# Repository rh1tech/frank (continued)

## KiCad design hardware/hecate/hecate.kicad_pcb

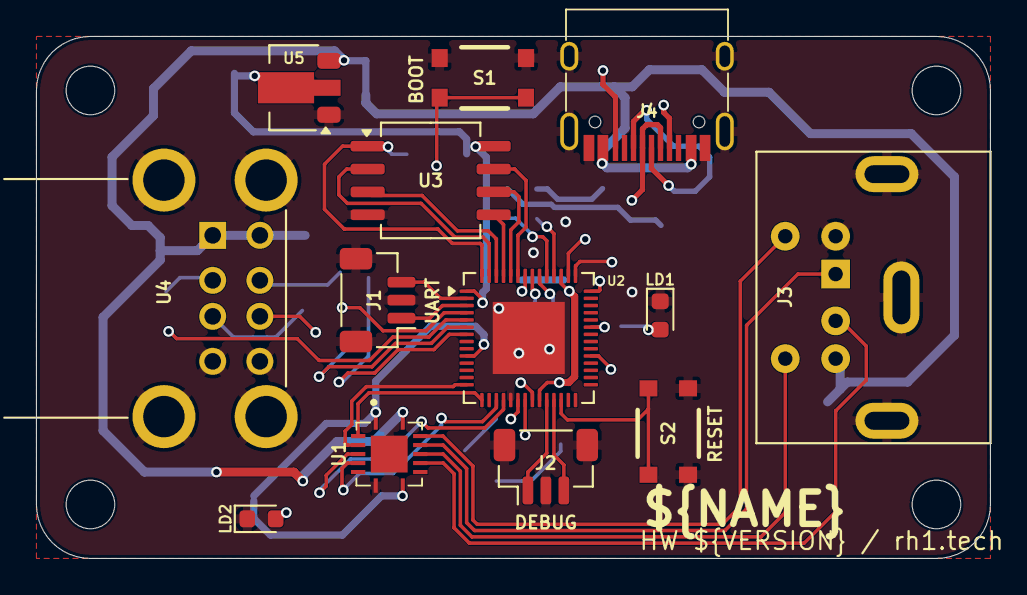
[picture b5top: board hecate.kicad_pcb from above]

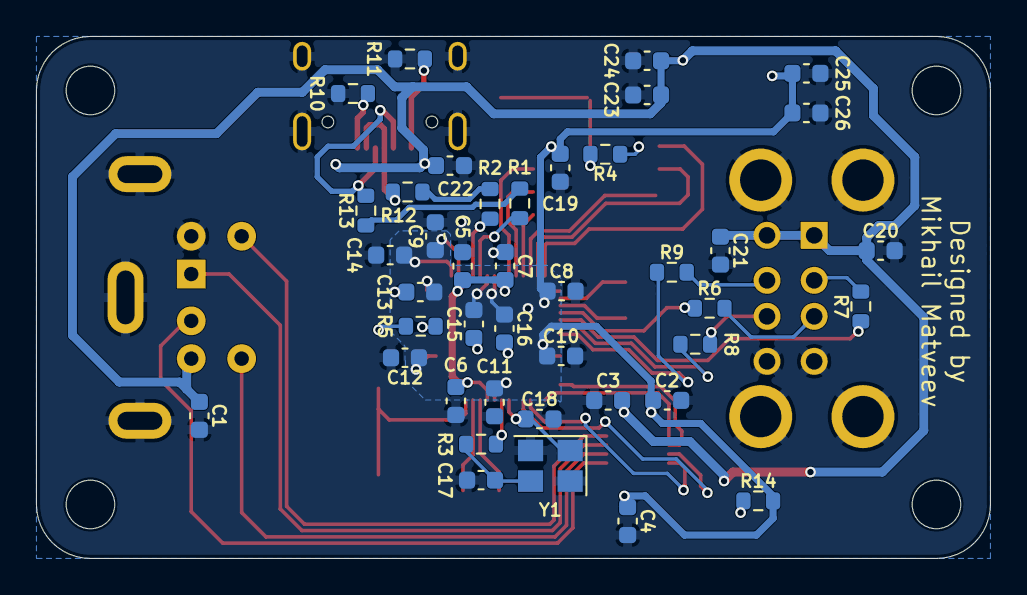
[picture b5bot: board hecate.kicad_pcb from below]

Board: 2 copper layers, 53.0 x 29.0 mm, 58 parts (41 on the bottom side), 46 nets.

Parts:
C1, C2, C3, C4, C5, C6, C8, C10, C11, C12, C13, C14, C15, C16, C19, C22, C24, C26: 100n; C_0603_1608Metric
C7, C9: 1u; C_0603_1608Metric
C17, C18: 15p; C_0603_1608Metric
C20, C21, C23, C25: 10u; C_0603_1608Metric
H1, H2, H3, H4: MountingHole; MountingHole_2.7mm
J1: UART; JST_SH_BM03B-SRSS-TB_1x03-1MP_P1.00mm_Vertical
J2: DEBUG; JST_SH_BM03B-SRSS-TB_1x03-1MP_P1.00mm_Vertical
J3: MDC-036; MiniDIN_6pin_Female
J4: USB4215-03-A; USB_C_Receptacle
LD1: Blue; LED_0603_1608Metric
LD2: Green; LED_0603_1608Metric
R1, R2: 27R; R_0603_1608Metric
R3, R4, R5, R14: 1K; R_0603_1608Metric
R6, R7, R8, R9, R12, R13: 22R; R_0603_1608Metric
R10, R11: 5.1K; R_0603_1608Metric
S1, S2: RP Reset; KMR_2
U1: TXS0104ERGYR; RGY_S-PVQFN-N14_
U2: RP2040; QFN-56-1EP_7x7mm_P0.4mm_EP4x4mm
U3: W25Q128JVSIQ; SOIC-8
U4: USB_A_Stacked
U5: AMS1117-3.3; SOT-89-3
Y1: 12 MHz; Crystal_SMD_3225-4Pin

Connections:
+3V3: C2.1, C4.1, C8.1, C9.1, C10.1, C11.1, C12.1, C13.1, C14.1, C15.1, C16.1, C19.1, C25.2, C26.2, R14.2, U1.1 (VCCA), U1.8 (OE), U2.1 (IOVDD), U2.10 (IOVDD), U2.22 (IOVDD), U2.33 (IOVDD), U2.42 (IOVDD), U2.43 (ADC_AVDD), U2.44 (VREG_IN), U2.48 (USB_VDD), U2.49 (IOVDD), U3.8 (VCC), U5.2 (VO)
/GPIO2: R6.1, U2.4 (GPIO2)
/GPIO3: R7.1, U2.5 (GPIO3)
/GPIO4: R8.1, U2.6 (GPIO4)
/GPIO5: R9.1, U2.7 (GPIO5)
/GPIO11: U1.3 (A2), U2.14 (GPIO11)
/GPIO12: U1.2 (A1), U2.15 (GPIO12)
/GPIO14: U1.5 (A4), U2.17 (GPIO14)
/GPIO15: U1.4 (A3), U2.18 (GPIO15)
/PS2/KB_CLK_5V: J3.5, U1.13 (B1)
/PS2/KB_DATA_5V: J3.1, U1.12 (B2)
/PS2/MS_CLK_5V: J3.6, U1.11 (B3)
/PS2/MS_DATA_5V: J3.2, U1.10 (B4)
/RP2040/BOOT: R4.2, S1.2, S1.4
/RP2040/D+: R1.1, R13.1
/RP2040/D-: R2.1, R12.1
/RP2040/GPIO0: J1.1, U2.2 (GPIO0)
/RP2040/GPIO1: J1.3, U2.3 (GPIO1)
/RP2040/GPIO25: R5.2, U2.37 (GPIO25)
/RP2040/QSPI_SCLK: U2.52 (QSPI_SCLK), U3.6 (CLK)
/RP2040/QSPI_SD0: U2.53 (QSPI_SD0), U3.5 (DI(IO0))
/RP2040/QSPI_SD1: U2.55 (QSPI_SD1), U3.2 (DO(IO1))
/RP2040/QSPI_SD2: U2.54 (QSPI_SD2), U3.3 (IO2)
/RP2040/QSPI_SD3: U2.51 (QSPI_SD3), U3.7 (IO3)
/RP2040/QSPI_SS: R4.1, U2.56 (QSPI_SS), U3.1 (~CS)
/RP2040/RUN: S2.2, S2.4, U2.26 (RUN)
/RP2040/SWCLK: J2.3, U2.24 (SWCLK)
/RP2040/SWD: J2.1, U2.25 (SWD)
/RP2040/XIN: C18.1, U2.20 (XIN), Y1.1
/RP2040/XOUT: R3.1, U2.21 (XOUT)
GND: C1.2, C2.2, C3.2, C4.2, C5.2, C6.2, C7.2, C8.2, C9.2, C10.2, C11.2, C12.2, C13.2, C14.2, C15.2, C16.2, C17.2, C18.2, C19.2, C20.2, C21.2, C22.1, C23.1, C24.1, C25.1, C26.1, J1.2, J2.2, J3.3, J4.1 (GND), J4.12 (GND), J4.13 (SHIELD), LD1.1 (K), LD2.1 (K), R10.1, R11.1, S1.1, S1.3, S2.1, S2.3, U1.7 (GND), U1.15 (THERMAL_PAD), U2.19 (TESTEN), U2.57 (GND), U3.4 (GND), U4.4 (GND1), U4.8 (GND2), U4.SH (Shield), U5.1 (GND), Y1.2 (G), Y1.4 (G)
unnamed: C17.1, R3.2, Y1.3
unnamed: J4.4 (CC1), R10.2
unnamed: J4.10 (CC2), R11.2
unnamed: J4.5 (DN2), J4.7 (DN1), R12.2
unnamed: J4.6 (DP1), J4.8 (DP2), R13.2
unnamed: LD1.2 (A), R5.1
unnamed: LD2.2 (A), R14.1
unnamed: R2.2, U2.46 (USB_DM)
unnamed: R1.2, U2.47 (USB_DP)
unnamed: C5.1, C6.1, C7.1, U2.23 (DVDD), U2.45 (VREG_VOUT), U2.50 (DVDD)
unnamed: R6.2, U4.3 (D1+)
unnamed: R7.2, U4.2 (D1-)
unnamed: R8.2, U4.7 (D2+)
unnamed: R9.2, U4.6 (D2-)
VBUS: C1.1, C3.1, C20.1, C21.1, C22.2, C23.2, C24.2, J3.4, J4.2 (VBUS), J4.11 (VBUS), U1.14 (VCCB), U4.1 (VBUS1), U4.5 (VBUS2), U5.3 (VI)

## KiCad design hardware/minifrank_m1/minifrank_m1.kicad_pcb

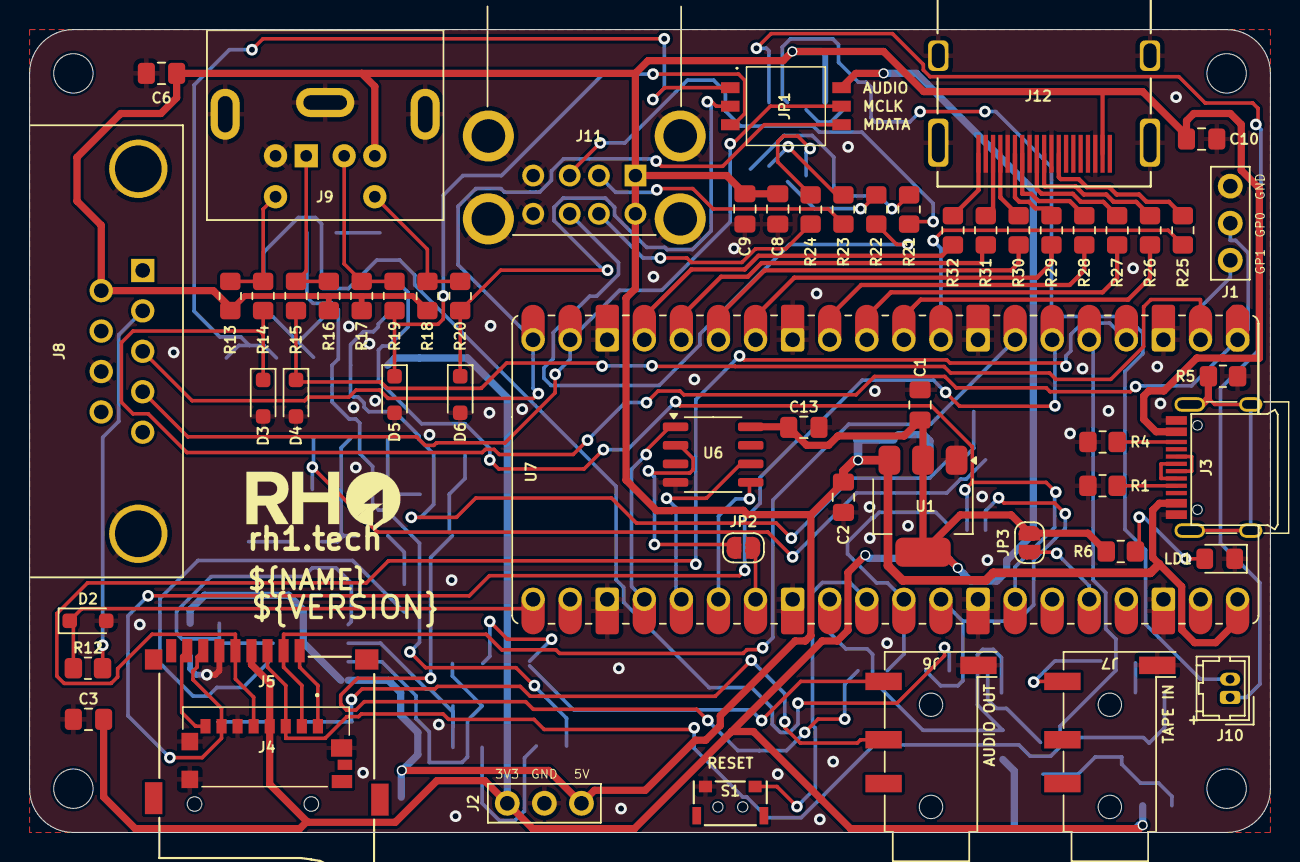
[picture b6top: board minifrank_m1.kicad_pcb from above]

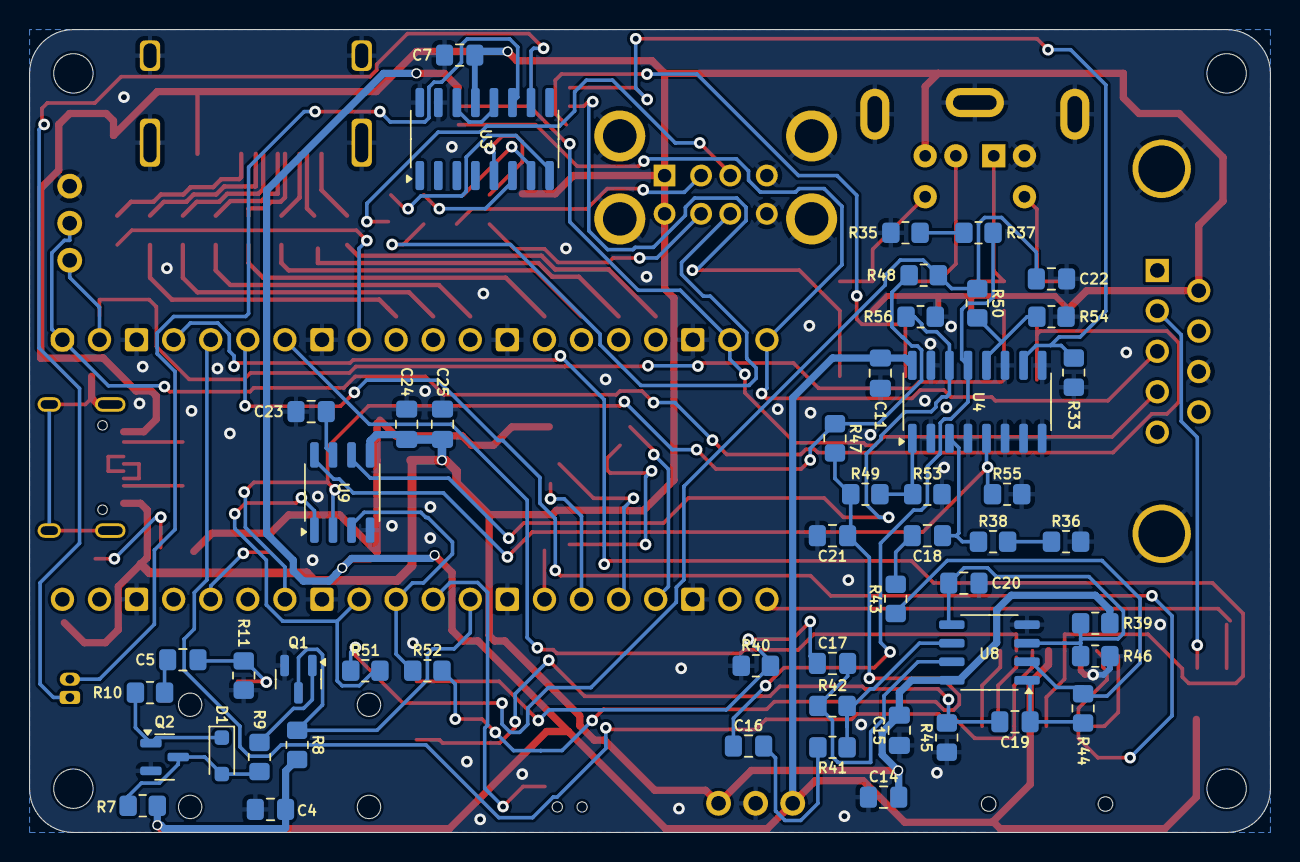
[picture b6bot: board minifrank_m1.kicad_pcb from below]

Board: 2 copper layers, 85.0 x 55.0 mm, 113 parts (51 on the bottom side), 91 nets.

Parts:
C1, C2, C8, C9, C14, C16, C17, C18, C19, C20, C23, C24: 10u; Capacitor (0805)
C3, C4, C5, C6, C10, C11, C13, C15, C25: 100n; Capacitor (0805)
C7: 4.7u; Capacitor (0805)
C21, C22: 47n; Capacitor (0805)
D1: 1N4148; Diode (SOD-323)
D2, D3, D4, D5, D6: 3V3; Diode (SOD-323)
H1, H2, H3, H4: MountingHole; Mounting Hole (2.7mm)
J1: UART; Pin Header (1x03)
J2: PWR; Pin Header (1x03)
J3: USB4215-03-A; USB Type C
J4: 0475710001; MicroSD (SMD, short)
J5: 104031-0811; MicroSD (SMD, long)
J6, J7: PJ-320D; Jack (3.5mm, PJ-320D)
J8: D-SUB 9 Male; D-SUB (9 pin, male, top mount)
J9: MDC-036; MiniDIN (6 Pin, female)
J10: USB HUB Data; Connector Female 1.25 JST 2P
J11: SS-52100-004; USB Type A (stacked)
J12: DC3RX19JA2; HDMI (female)
JP1: Main Jumpers; DS05127203BKSMTTR
JP2, JP3: Jumper (Solder); Jumper (solder)
LD1: Power; LED (0805)
Q1, Q2: BC850; SOT-23
R1, R4: 5.1K; Resistor (0805)
R5: 1M; Resistor (0805)
R6, R8, R12, R13, R16, R17, R18, R51, R52: 1K; Resistor (0805)
R7, R9, R10, R33, R37, R38, R39, R41, R43, R46, R49, R50: 10K; Resistor (0805)
R11, R14, R15, R19, R20: 100R; Resistor (0805)
R21, R22, R23, R24: 22R; Resistor (0805)
R25, R26, R27, R28, R29, R30, R31, R32: 270R; Resistor (0805)
R35, R36, R47, R48, R53, R54: 2K; Resistor (0805)
R40, R45: 20K; Resistor (0805)
R42, R44: 47K; Resistor (0805)
R55, R56: 470R; Resistor (0805)
S1: Reset; TACT-SIDE-4623
U1: NCP1117 3.3; SOT-223
U3: MW7211A; SOP-16
U4: 74HC4052D; SOP-16
U6: ESP-PSRAM32; SO-8
U7: Rasberry Pi Pico; Raspberry Pi Pico
U8: LM358; SO-8
U9: TDA1387T; SO-8

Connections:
+3V3: C1.1, C3.2, C4.1, C11.2, C13.1, J2.1, J4.P4 (VDD), J5.4 (VDD), JP1.6, JP3.2 (B), R6.2, R7.1, R8.1, U1.2 (VO), U4.16 (VCC), U6.8 (VCC)
/AMP_IN_L: C16.1, R37.1, U4.13 (1Z)
/AMP_IN_R: C18.1, R38.1, U4.3 (2Z)
/AUDIOSW: JP1.1, R33.2, U4.10 (S0)
/Audio Out/AMP_OUTL: C17.2, J6.T, R40.2
/Audio Out/AMP_OUTR: C19.2, J6.R, R45.2
/GPIO0: D3.1 (K), J1.2, R14.2, U7.1 (GPIO0)
/GPIO1: D4.1 (K), J1.3, R15.2, U7.2 (GPIO1)
/GPIO2: J4.P5 (CLK), J5.5 (CLK), U7.4 (GPIO2)
/GPIO3: J4.P3 (CMD), J5.3 (CMD), U7.5 (GPIO3)
/GPIO4: J4.P7 (DAT0), J5.7 (DAT0), U7.6 (GPIO4)
/GPIO5: J4.P2 (CD/DAT3), J5.2 (DAT3/CD), U7.7 (GPIO5)
/GPIO6: R25.2, U7.9 (GPIO6)
/GPIO7: R26.2, U7.10 (GPIO7)
/GPIO8: R27.2, U7.11 (GPIO8)
/GPIO9: R28.2, U7.12 (GPIO9)
/GPIO10: R29.2, U7.14 (GPIO10)
/GPIO11: R30.2, U7.15 (GPIO11)
/GPIO12: R31.2, U7.16 (GPIO12)
/GPIO13: R32.2, U7.17 (GPIO13)
/GPIO14: J8.4, JP1.5, U7.19 (GPIO14)
/GPIO15: J8.3, JP1.4, U7.20 (GPIO15)
/GPIO16: D2.1 (K), R12.1, U7.21 (GPIO16)
/GPIO18: U6.1 (~CE), U7.24 (GPIO18)
/GPIO19: U6.6 (SCLK), U7.25 (GPIO19)
/GPIO20: U6.5 (SI/SIO), U7.26 (GPIO20)
/GPIO21: JP2.2 (B), U7.27 (GPIO21)
/GPIO22: Q1.3 (C), R8.2, U7.29 (GPIO22)
/GPIO26: R52.2, U7.31 (GPIO26_ADC0), U9.3 (DATA)
/GPIO27: R51.2, U7.32 (GPIO27_ADC1), U9.1 (SCLK)
/GPIO28: R47.1, R48.1, U7.34 (GPIO28_ADC2), U9.2 (LRCK)
/KB_CLK: J9.5, R13.2, R14.1
/KB_DATA: J9.1, R15.1, R16.2
/MS_CLK: J9.6, R18.2, R20.1
/MS_CLK_3V: D6.1 (K), JP1.2, R20.2
/MS_DATA: J9.2, R17.2, R19.1
/MS_DATA_3V: D5.1 (K), JP1.3, R19.2
/PWM_OUT_L: R50.2, R54.1, U4.12 (1Y0)
/PWM_OUT_R: R49.2, R53.1, U4.1 (2Y0)
/Power/D+: J3.6 (DP1), J3.8 (DP2)
/Power/D-: J3.5 (DN2), J3.7 (DN1)
/RUN: S1.1, U7.30 (RUN)
/SD Card/DAT1: J4.P8 (DAT1), J5.8 (DAT1)
/SD Card/DAT2: J4.P1 (DAT2), J5.1 (DAT2)
/TDA_L: R56.2, U4.14 (1Y1), U9.6 (A_LEFT)
/TDA_R: R55.1, U4.5 (2Y1), U9.8 (A_RIGHT)
/USB Hub/DM_IN: J10.2, U3.10 (DMU)
/USB Hub/DP_IN: J10.1, U3.11 (DPU)
/USB_D1+: R21.1, U3.8 (DP3)
/USB_D1-: R23.1, U3.7 (DM3)
/USB_D2+: R22.1, U3.6 (DP2)
/USB_D2-: R24.1, U3.5 (DM2)
GND: C1.2, C2.2, C3.1, C4.2, C6.2, C7.2, C8.2, C9.2, C10.2, C11.1, C13.2, C14.1, C15.1, C20.1, C21.2, C22.2, C23.2, C24.2, C25.2, D2.2 (A), D3.2 (A), D4.2 (A), D5.2 (A), D6.2 (A), J1.1, J2.2, J3.1 (GND), J3.12 (GND), J4.G1 (GND_1), J4.G2 (GND_2), J4.G3 (GND_3), J4.P6 (VSS), J5.6 (VSS), J6.S, J7.S, J8.8, J9.3, J11.4 (GND1), J11.8 (GND2), J11.9 (Shield), J12.2 (G_D2), J12.5 (G_D1), J12.8 (G_D0), J12.11 (G_CLK), J12.17 (G_DDC/CEC), J12.20 (SHIELD1), J12.21 (SHIELD2), J12.22 (SHIELD3), J12.23 (SHIELD4), LD1.1 (K), Q1.2 (E), Q2.2 (E), R1.1, R4.1, R5.2, R11.2, R33.1, R35.2, R36.2, R40.1, R45.1, R46.1, R53.2, R54.2, R55.2, R56.1, S1.2, U1.1 (GND), U3.15 (GND), U3.16 (GND), U4.2 (2Y2), U4.4 (2Y3), U4.6 (~E), U4.7 (VEE), U4.8 (GND), U4.9 (S1), U4.11 (1Y3), U4.15 (1Y2), U6.4 (VSS), U7.3 (GND), U7.8 (GND), U7.13 (GND), U7.18 (GND), U7.23 (GND), U7.28 (GND), U7.33 (AGND), U7.38 (GND), U8.4 (V-), U9.4 (AGND)
unnamed: C5.1, J7.T, R11.1
unnamed: C5.2, R10.1
unnamed: C16.2, R41.2
unnamed: C17.1, R42.1, U8.7
unnamed: C18.2, R43.2
unnamed: C19.1, R44.1, U8.1
unnamed: C21.1, R47.2, R49.1, R52.1
unnamed: C22.1, R48.2, R50.1, R51.1
unnamed: D1.2 (A), Q2.3 (C), R7.2, R9.1
unnamed: D1.1 (K), Q2.1 (B), R10.2
unnamed: J3.4 (CC1), R1.2
unnamed: J3.10 (CC2), R4.2
unnamed: J3.13 (SHIELD), R5.1
unnamed: J8.2, R12.2
unnamed: J11.3 (D1+), R21.2
unnamed: J11.2 (D1-), R23.2
unnamed: J11.7 (D2+), R22.2
unnamed: J11.6 (D2-), R24.2
unnamed: J12.12 (CLKN), R25.1
unnamed: J12.10 (CLKP), R26.1
unnamed: J12.9 (D0N), R27.1
unnamed: J12.7 (D0P), R28.1
unnamed: J12.6 (D1N), R29.1
unnamed: J12.4 (D1P), R30.1
unnamed: J12.3 (D2N), R31.1
unnamed: J12.1 (D2P), R32.1
unnamed: JP2.1 (A), U6.2 (SO/SIO)
unnamed: JP3.1 (A), U7.36 (3V3)
unnamed: LD1.2 (A), R6.1
unnamed: Q1.1 (B), R9.2
unnamed: R35.1, R37.2
unnamed: R36.1, R38.2
unnamed: U3.12 (VD33), U3.14 (VD3)
unnamed: C20.2, R39.1, R46.2, U8.3 (+), U8.5 (+)
unnamed: R43.1, R44.2, U8.2 (-)
unnamed: R41.1, R42.2, U8.6 (-)
unnamed: C23.1, U9.7 (FLT)
VBUS: C2.1, C6.1, C7.1, C8.1, C9.1, C10.1, C14.2, C15.2, C24.1, C25.1, J2.3, J3.2 (VBUS), J3.11 (VBUS), J8.6, J9.4, J11.1 (VBUS1), J11.5 (VBUS2), J12.18 (+5V), R13.1, R16.1, R17.1, R18.1, R39.2, U1.3 (VI), U3.13 (VDD5), U7.40 (VBUS), U8.8 (V+), U9.5 (VA)

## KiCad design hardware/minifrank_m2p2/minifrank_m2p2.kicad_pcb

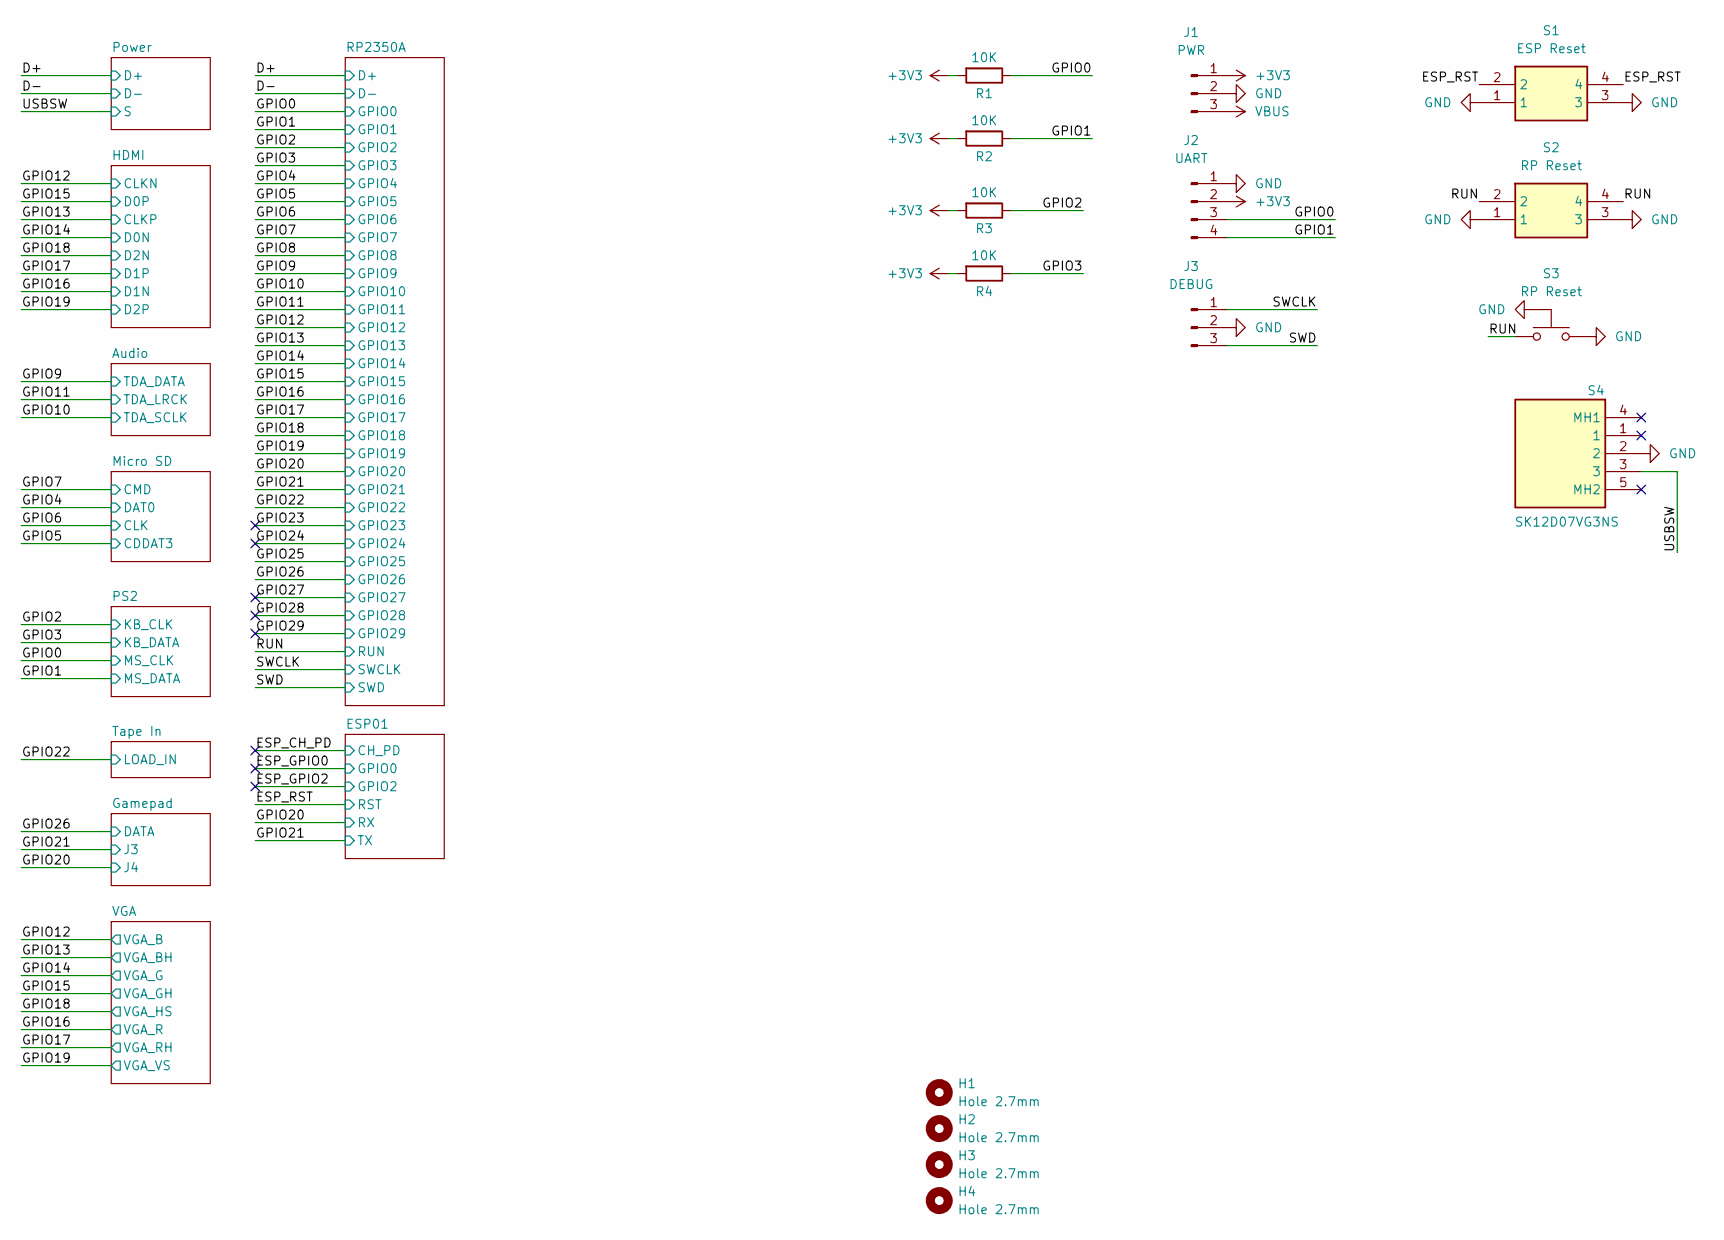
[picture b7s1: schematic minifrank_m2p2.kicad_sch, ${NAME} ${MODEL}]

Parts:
H1, H2, H3, H4: Hole 2.7mm; Mounting Hole (2.7mm)
J1: PWR; Pin Header (1x03)
J2: UART; JST_SH_BM04B-SRSS-TB_1x04-1MP_P1.00mm_Vertical
J3: DEBUG; JST_SH_BM03B-SRSS-TB_1x03-1MP_P1.00mm_Vertical
R1, R2, R3, R4: 10K; R_0603_1608Metric
S1: ESP Reset; KMR_2; Mouser Part Number 611-KMR221G-LFS
S2: RP Reset; KMR_2; Mouser Part Number 611-KMR221G-LFS
S3: RP Reset; TS-1234VW
S4: SK12D07VG3NS; Mouser Part Number 611-SK12D07VG3NS

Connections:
+3V3: J1.1, J2.2, R1.2, R2.2, R3.2, R4.2; also elsewhere on the board
/ESP_RST: S1.2, S1.4; also elsewhere on the board
/GPIO0: J2.3, R1.1; also elsewhere on the board
/GPIO1: J2.4, R2.1; also elsewhere on the board
/GPIO2: R3.1; also elsewhere on the board
/GPIO3: R4.1; also elsewhere on the board
/RUN: S2.2, S2.4, S3.1; also elsewhere on the board
/SWCLK: J3.1; also elsewhere on the board
/SWD: J3.3; also elsewhere on the board
/USBSW: S4.3; also elsewhere on the board
GND: J1.2, J2.1, J3.2, S1.1, S1.3, S2.1, S2.3, S3.2, S3.3 (GND), S4.2; also elsewhere on the board
VBUS: J1.3; also elsewhere on the board

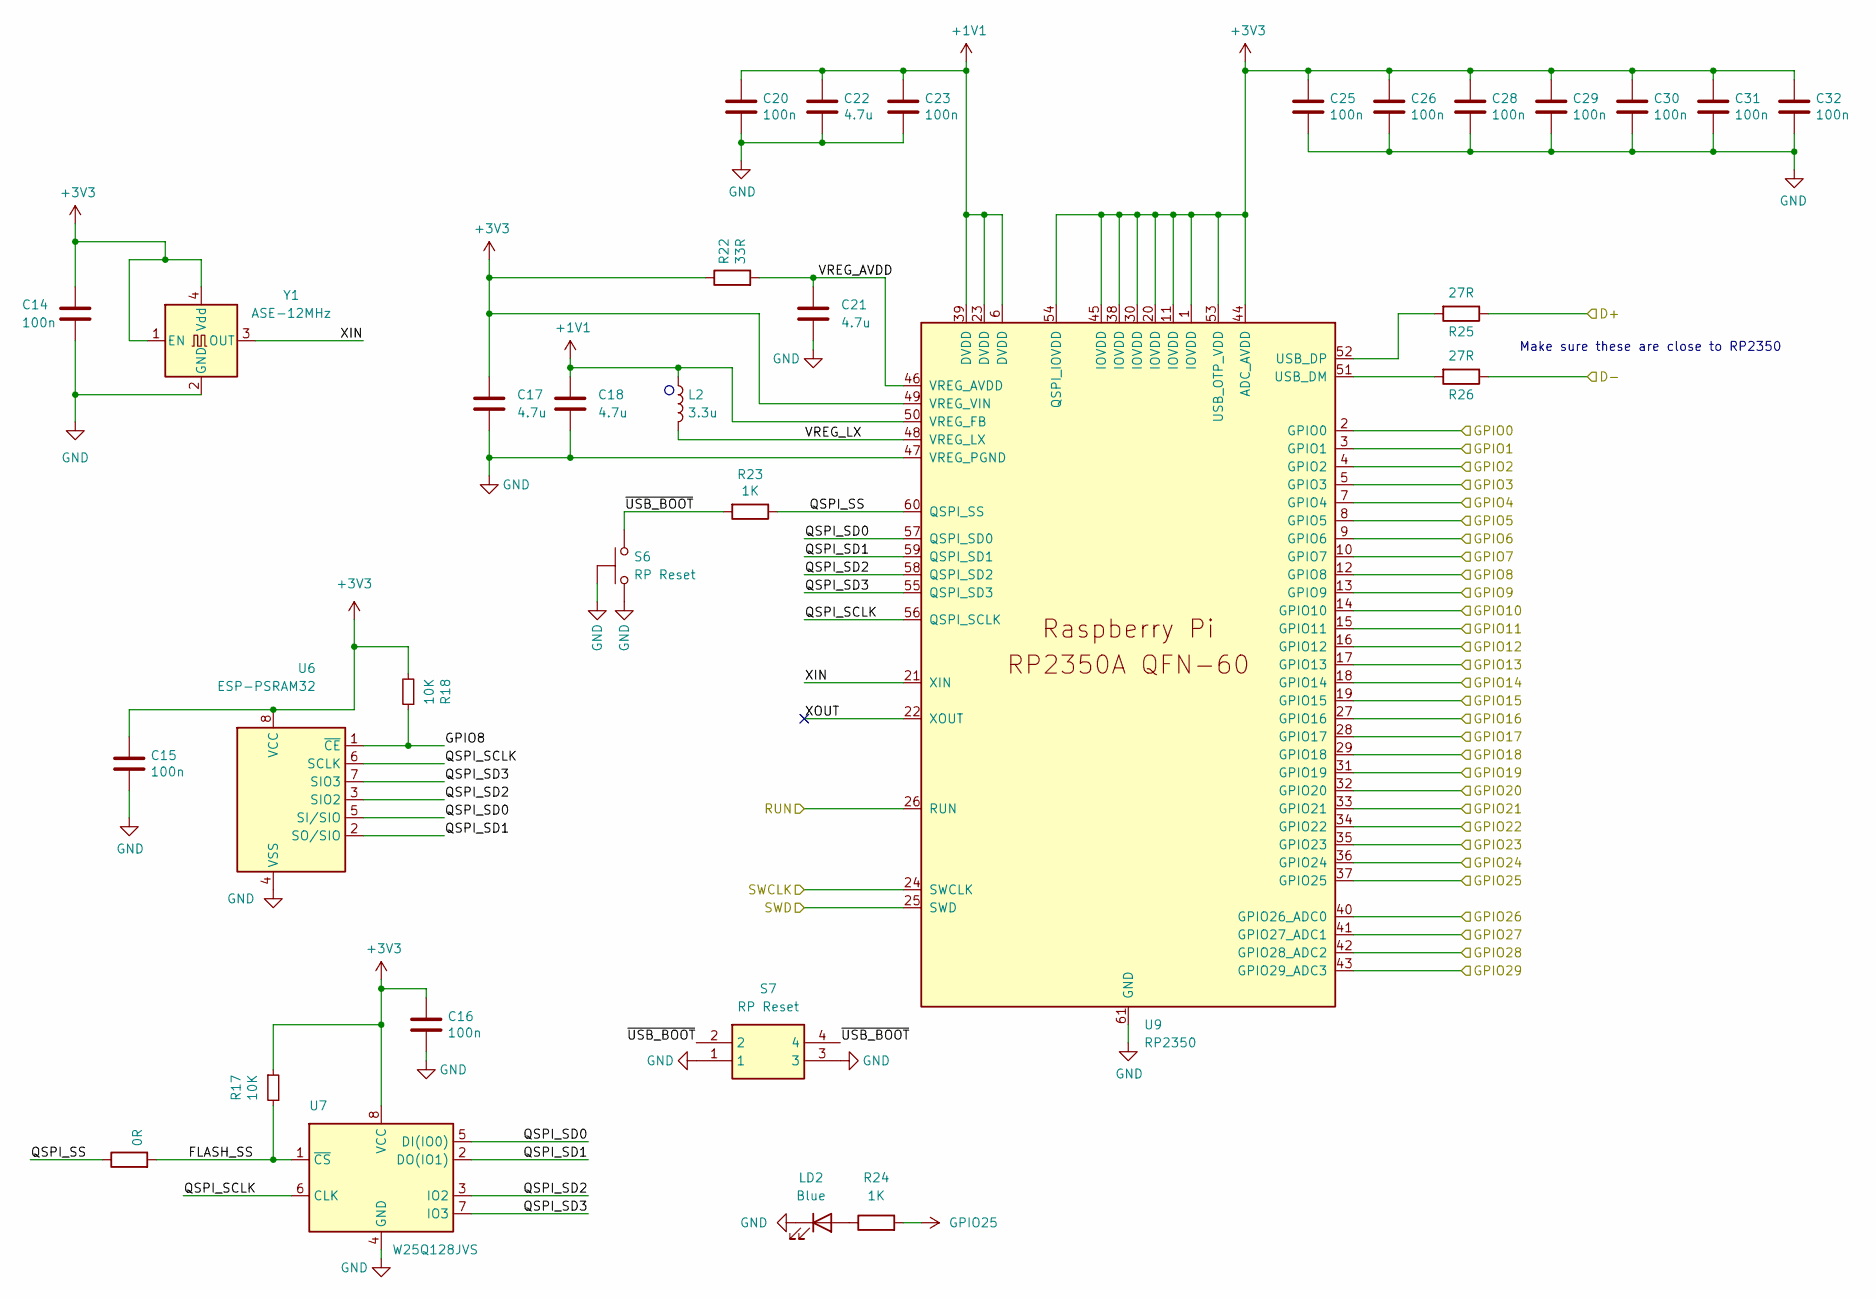
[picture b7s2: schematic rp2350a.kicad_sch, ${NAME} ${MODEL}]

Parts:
C14, C15, C16, C20, C23, C25, C26, C28, C29, C30, C31, C32: 100n; C_0603_1608Metric
C17, C18, C21, C22: 4.7u; C_0603_1608Metric
L2: 3.3u; L_pol_2016
LD2: Blue; LED_0603_1608Metric
R16: 0R; R_0603_1608Metric
R17, R18: 10K; R_0603_1608Metric
R22: 33R; R_0603_1608Metric
R23, R24: 1K; R_0603_1608Metric
R25, R26: 27R; R_0603_1608Metric
S6: RP Reset; TS-1234VW
S7: RP Reset; KMR_2; Mouser Part Number 611-KMR221G-LFS
U6: ESP-PSRAM32; SO-8
U7: W25Q128JVS; SOIC-8
U9: RP2350; QFN 60 (RP2350A)
Y1: ASE-12MHz; Oscillator_SMD_Abracon_ASE-4Pin_3.2x2.5mm

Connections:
+1V1: C18.1, C20.1, C22.1, C23.1, L2.1, U9.6 (DVDD), U9.23 (DVDD), U9.39 (DVDD), U9.50 (VREG_FB)
+3V3: C14.1, C15.1, C16.1, C17.1, C25.1, C26.1, C28.1, C29.1, C30.1, C31.1, C32.1, R17.1, R18.2, R22.1, U6.8 (VCC), U7.8 (VCC), U9.1 (IOVDD), U9.11 (IOVDD), U9.20 (IOVDD), U9.30 (IOVDD), U9.38 (IOVDD), U9.44 (ADC_AVDD), U9.45 (IOVDD), U9.49 (VREG_VIN), U9.53 (USB_OTP_VDD), U9.54 (QSPI_IOVDD), Y1.1 (EN), Y1.4 (Vdd); also elsewhere on the board
/D+: R25.1; also elsewhere on the board
/D-: R26.1; also elsewhere on the board
/GPIO0: U9.2 (GPIO0); also elsewhere on the board
/GPIO1: U9.3 (GPIO1); also elsewhere on the board
/GPIO2: U9.4 (GPIO2); also elsewhere on the board
/GPIO3: U9.5 (GPIO3); also elsewhere on the board
/GPIO4: U9.7 (GPIO4); also elsewhere on the board
/GPIO5: U9.8 (GPIO5); also elsewhere on the board
/GPIO6: U9.9 (GPIO6); also elsewhere on the board
/GPIO7: U9.10 (GPIO7); also elsewhere on the board
/GPIO8: R18.1, U6.1 (~CE), U9.12 (GPIO8)
/GPIO9: U9.13 (GPIO9); also elsewhere on the board
/GPIO10: U9.14 (GPIO10); also elsewhere on the board
/GPIO11: U9.15 (GPIO11); also elsewhere on the board
/GPIO12: U9.16 (GPIO12); also elsewhere on the board
/GPIO13: U9.17 (GPIO13); also elsewhere on the board
/GPIO14: U9.18 (GPIO14); also elsewhere on the board
/GPIO15: U9.19 (GPIO15); also elsewhere on the board
/GPIO16: U9.27 (GPIO16); also elsewhere on the board
/GPIO17: U9.28 (GPIO17); also elsewhere on the board
/GPIO18: U9.29 (GPIO18); also elsewhere on the board
/GPIO19: U9.31 (GPIO19); also elsewhere on the board
/GPIO20: U9.32 (GPIO20); also elsewhere on the board
/GPIO21: U9.33 (GPIO21); also elsewhere on the board
/GPIO22: U9.34 (GPIO22); also elsewhere on the board
/GPIO23: U9.35 (GPIO23)
/GPIO24: U9.36 (GPIO24)
/GPIO26: U9.40 (GPIO26_ADC0); also elsewhere on the board
/GPIO27: U9.41 (GPIO27_ADC1)
/GPIO28: U9.42 (GPIO28_ADC2)
/GPIO29: U9.43 (GPIO29_ADC3)
/RP2350A/FLASH_SS: R16.2, R17.2, U7.1 (~CS)
/RP2350A/QSPI_SCLK: U6.6 (SCLK), U7.6 (CLK), U9.56 (QSPI_SCLK)
/RP2350A/QSPI_SD0: U6.5 (SI/SIO), U7.5 (DI(IO0)), U9.57 (QSPI_SD0)
/RP2350A/QSPI_SD1: U6.2 (SO/SIO), U7.2 (DO(IO1)), U9.59 (QSPI_SD1)
/RP2350A/QSPI_SD2: U6.3 (SIO2), U7.3 (IO2), U9.58 (QSPI_SD2)
/RP2350A/QSPI_SD3: U6.7 (SIO3), U7.7 (IO3), U9.55 (QSPI_SD3)
/RP2350A/QSPI_SS: R16.1, R23.1, U9.60 (QSPI_SS)
/RP2350A/VREG_AVDD: C21.1, R22.2, U9.46 (VREG_AVDD)
/RP2350A/VREG_LX: L2.2, U9.48 (VREG_LX)
/RP2350A/XIN: U9.21 (XIN), Y1.3 (OUT)
/RP2350A/XOUT: U9.22 (XOUT)
/RP2350A/~USB_BOOT: R23.2, S6.2, S7.2, S7.4
/RUN: U9.26 (RUN); also elsewhere on the board
/SWCLK: U9.24 (SWCLK); also elsewhere on the board
/SWD: U9.25 (SWD); also elsewhere on the board
GND: C14.2, C15.2, C16.2, C17.2, C18.2, C20.2, C21.2, C22.2, C23.2, C25.2, C26.2, C28.2, C29.2, C30.2, C31.2, C32.2, LD2.1 (K), S6.1, S6.3 (GND), S7.1, S7.3, U6.4 (VSS), U7.4 (GND), U9.47 (VREG_PGND), U9.61 (GND), Y1.2 (GND); also elsewhere on the board
GPIO25: R24.2, U9.37 (GPIO25)
unnamed: LD2.2 (A), R24.1
unnamed: R26.2, U9.51 (USB_DM)
unnamed: R25.2, U9.52 (USB_DP)

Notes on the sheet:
Make sure these are close to RP2350

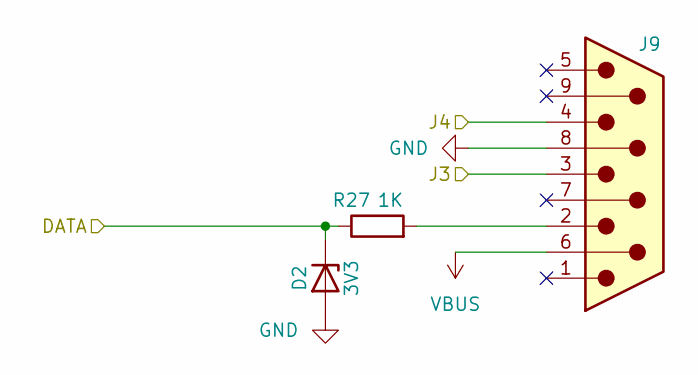
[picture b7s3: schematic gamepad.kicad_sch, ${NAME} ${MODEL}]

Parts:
D2: 3V3; Diode (SOD-323)
J9: GP2; D-SUB (9 pin, male, top mount)
R27: 1K; R_0603_1608Metric

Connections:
/GPIO20: J9.4; also elsewhere on the board
/GPIO21: J9.3; also elsewhere on the board
/GPIO26: D2.1 (K), R27.1; also elsewhere on the board
GND: D2.2 (A), J9.8; also elsewhere on the board
unnamed: J9.2, R27.2
VBUS: J9.6; also elsewhere on the board

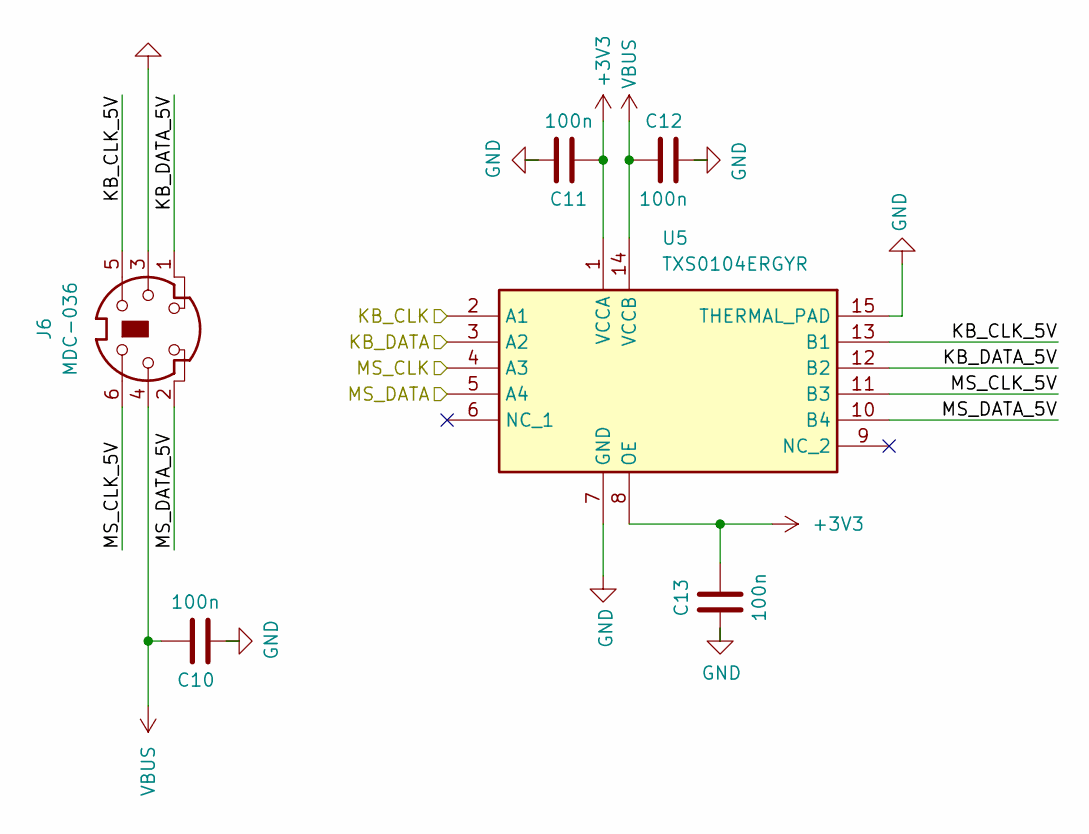
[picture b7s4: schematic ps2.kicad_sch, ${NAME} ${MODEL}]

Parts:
C10, C11, C12, C13: 100n; C_0603_1608Metric
J6: MDC-036; MiniDIN (6 Pin, female)
U5: TXS0104ERGYR; RGY_S-PVQFN-N14_; Mouser Part Number 595-TXS0104ERGYR

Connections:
+3V3: C11.1, C13.1, U5.1 (VCCA), U5.8 (OE); also elsewhere on the board
/GPIO0: U5.4 (A3); also elsewhere on the board
/GPIO1: U5.5 (A4); also elsewhere on the board
/GPIO2: U5.2 (A1); also elsewhere on the board
/GPIO3: U5.3 (A2); also elsewhere on the board
/PS2/KB_CLK_5V: J6.5, U5.13 (B1)
/PS2/KB_DATA_5V: J6.1, U5.12 (B2)
/PS2/MS_CLK_5V: J6.6, U5.11 (B3)
/PS2/MS_DATA_5V: J6.2, U5.10 (B4)
GND: C10.2, C11.2, C12.2, C13.2, J6.3, U5.7 (GND), U5.15 (THERMAL_PAD); also elsewhere on the board
VBUS: C10.1, C12.1, J6.4, U5.14 (VCCB); also elsewhere on the board

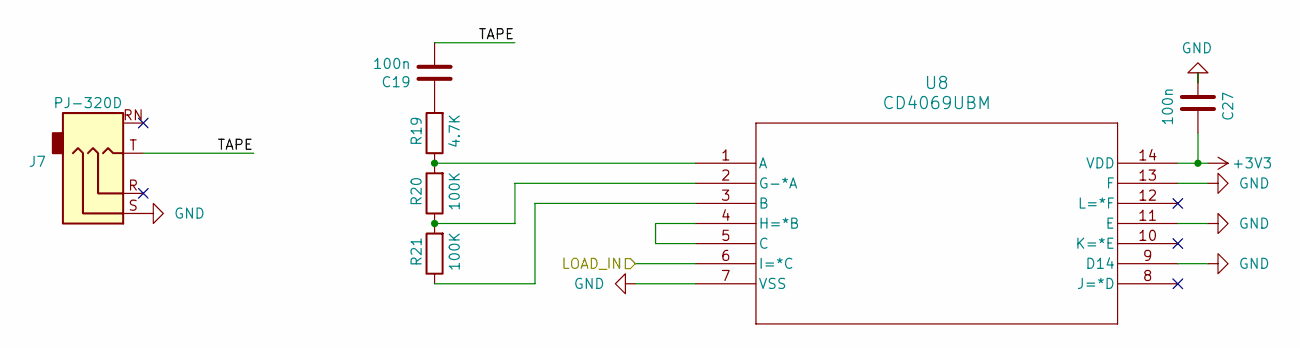
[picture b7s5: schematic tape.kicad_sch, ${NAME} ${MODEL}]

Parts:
C19, C27: 100n; C_0603_1608Metric
J7: PJ-320D; Jack (3.5mm, PJ-320D)
R19: 4.7K; R_0603_1608Metric
R20, R21: 100K; R_0603_1608Metric
U8: CD4069UBM; SOIC127P600X175-14N

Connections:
+3V3: C27.1, U8.14 (VDD); also elsewhere on the board
/GPIO22: U8.6 (I=*C); also elsewhere on the board
/Tape In/TAPE: C19.2, J7.T
GND: C27.2, J7.S, U8.7 (VSS), U8.9 (D14), U8.11 (E), U8.13 (F); also elsewhere on the board
unnamed: C19.1, R19.2
unnamed: R19.1, R20.2, U8.1 (A)
unnamed: R21.1, U8.3 (B)
unnamed: U8.4 (H=*B), U8.5 (C)
unnamed: R20.1, R21.2, U8.2 (G-*A)

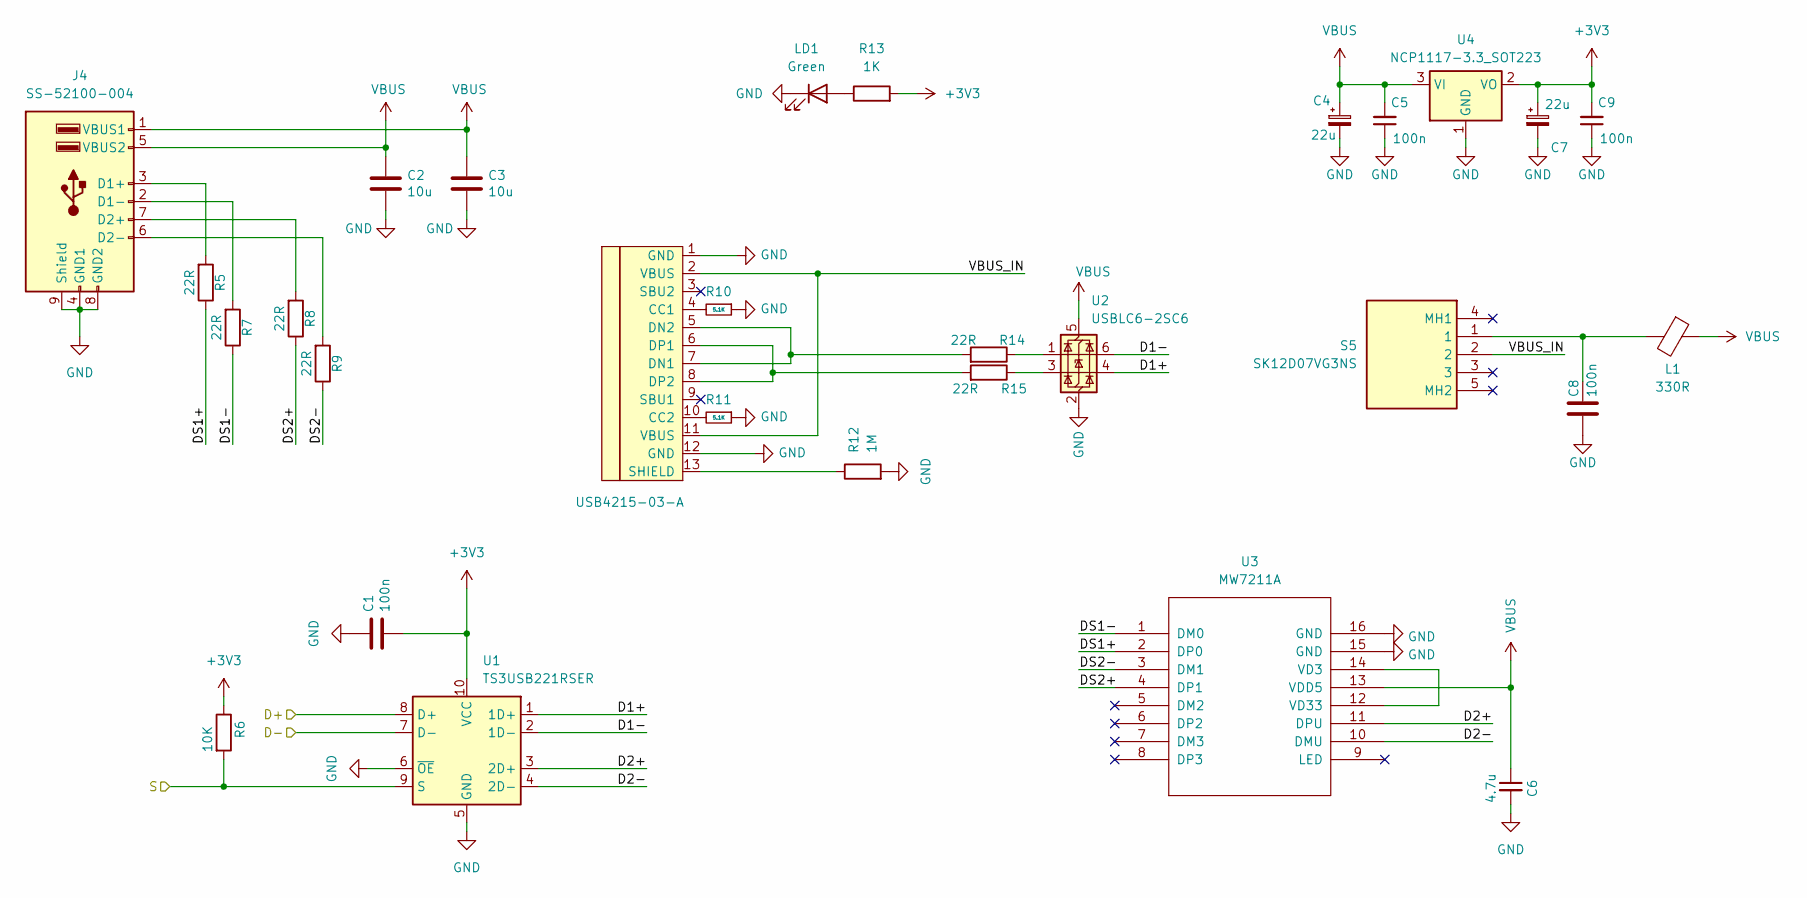
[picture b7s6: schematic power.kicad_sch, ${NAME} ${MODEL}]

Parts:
C1, C5, C8, C9: 100n; C_0603_1608Metric
C2, C3: 10u; C_0603_1608Metric
C4, C7: 22u; Capacitor (3528, tantalum, polar)
C6: 4.7u; C_0603_1608Metric; LCSC C1746
J4: SS-52100-004; USB Type A (stacked)
J5: USB4215-03-A; USB Type C; LCSC C165948
L1: 330R; L_0603_1608Metric
LD1: Green; LED_0603_1608Metric
R5, R7, R8, R9, R14, R15: 22R; R_0603_1608Metric
R6: 10K; R_0603_1608Metric
R10, R11: 5.1K; R_0603_1608Metric
R12: 1M; R_0603_1608Metric
R13: 1K; R_0603_1608Metric
S5: SK12D07VG3NS; Mouser Part Number 611-SK12D07VG3NS
U1: TS3USB221RSER; UQFN-10
U2: USBLC6-2SC6; SOT-23-6
U3: MW7211A; SOP-16
U4: NCP1117-3.3_SOT223; SOT-223-3_TabPin2

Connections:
+3V3: C1.2, C7.1, C9.2, R6.1, R13.2, U1.10 (VCC), U4.2 (VO); also elsewhere on the board
/D+: U1.8 (D+); also elsewhere on the board
/D-: U1.7 (D-); also elsewhere on the board
/Power/D1+: U1.1 (1D+), U2.4 (I/O2)
/Power/D1-: U1.2 (1D-), U2.6 (I/O1)
/Power/D2+: U1.3 (2D+), U3.11 (DPU)
/Power/D2-: U1.4 (2D-), U3.10 (DMU)
/Power/DS1+: R5.1, U3.2 (DP0)
/Power/DS1-: R7.1, U3.1 (DM0)
/Power/DS2+: R8.1, U3.4 (DP1)
/Power/DS2-: R9.1, U3.3 (DM1)
/Power/VBUS_IN: J5.2 (VBUS), J5.11 (VBUS), S5.2
/USBSW: R6.2, U1.9 (S); also elsewhere on the board
GND: C1.1, C2.2, C3.2, C4.2, C5.1, C6.2, C7.2, C8.2, C9.1, J4.4 (GND1), J4.8 (GND2), J4.9 (Shield), J5.1 (GND), J5.12 (GND), LD1.1 (K), R10.1, R11.1, R12.2, U1.5 (GND), U1.6 (~OE), U2.2 (GND), U3.15 (GND), U3.16 (GND), U4.1 (GND); also elsewhere on the board
unnamed: C8.1, L1.2, S5.1
unnamed: J4.3 (D1+), R5.2
unnamed: J4.2 (D1-), R7.2
unnamed: J4.7 (D2+), R8.2
unnamed: J4.6 (D2-), R9.2
unnamed: J5.4 (CC1), R10.2
unnamed: J5.10 (CC2), R11.2
unnamed: J5.5 (DN2), J5.7 (DN1), R14.2
unnamed: J5.6 (DP1), J5.8 (DP2), R15.2
unnamed: J5.13 (SHIELD), R12.1
unnamed: LD1.2 (A), R13.1
unnamed: R14.1, U2.1 (I/O1)
unnamed: R15.1, U2.3 (I/O2)
unnamed: U3.12 (VD33), U3.14 (VD3)
VBUS: C2.1, C3.1, C4.1, C5.2, C6.1, J4.1 (VBUS1), J4.5 (VBUS2), L1.1, U2.5 (VBUS), U3.13 (VDD5), U4.3 (VI); also elsewhere on the board

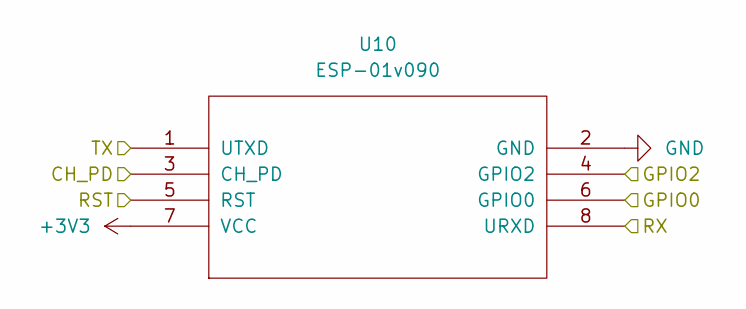
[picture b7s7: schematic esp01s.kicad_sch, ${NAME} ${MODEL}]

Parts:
U10: ESP-01v090; ESP-01

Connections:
+3V3: U10.7 (VCC); also elsewhere on the board
/ESP_CH_PD: U10.3 (CH_PD)
/ESP_GPIO0: U10.6 (GPIO0)
/ESP_GPIO2: U10.4 (GPIO2)
/ESP_RST: U10.5 (RST); also elsewhere on the board
/GPIO20: U10.8 (URXD); also elsewhere on the board
/GPIO21: U10.1 (UTXD); also elsewhere on the board
GND: U10.2 (GND); also elsewhere on the board
